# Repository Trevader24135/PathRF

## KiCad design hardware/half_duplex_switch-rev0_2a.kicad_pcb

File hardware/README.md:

# Hardware

The hardware for the PathRF was designed using KiCad 7.0 (available to download for free [here](https://www.kicad.org/download/)).

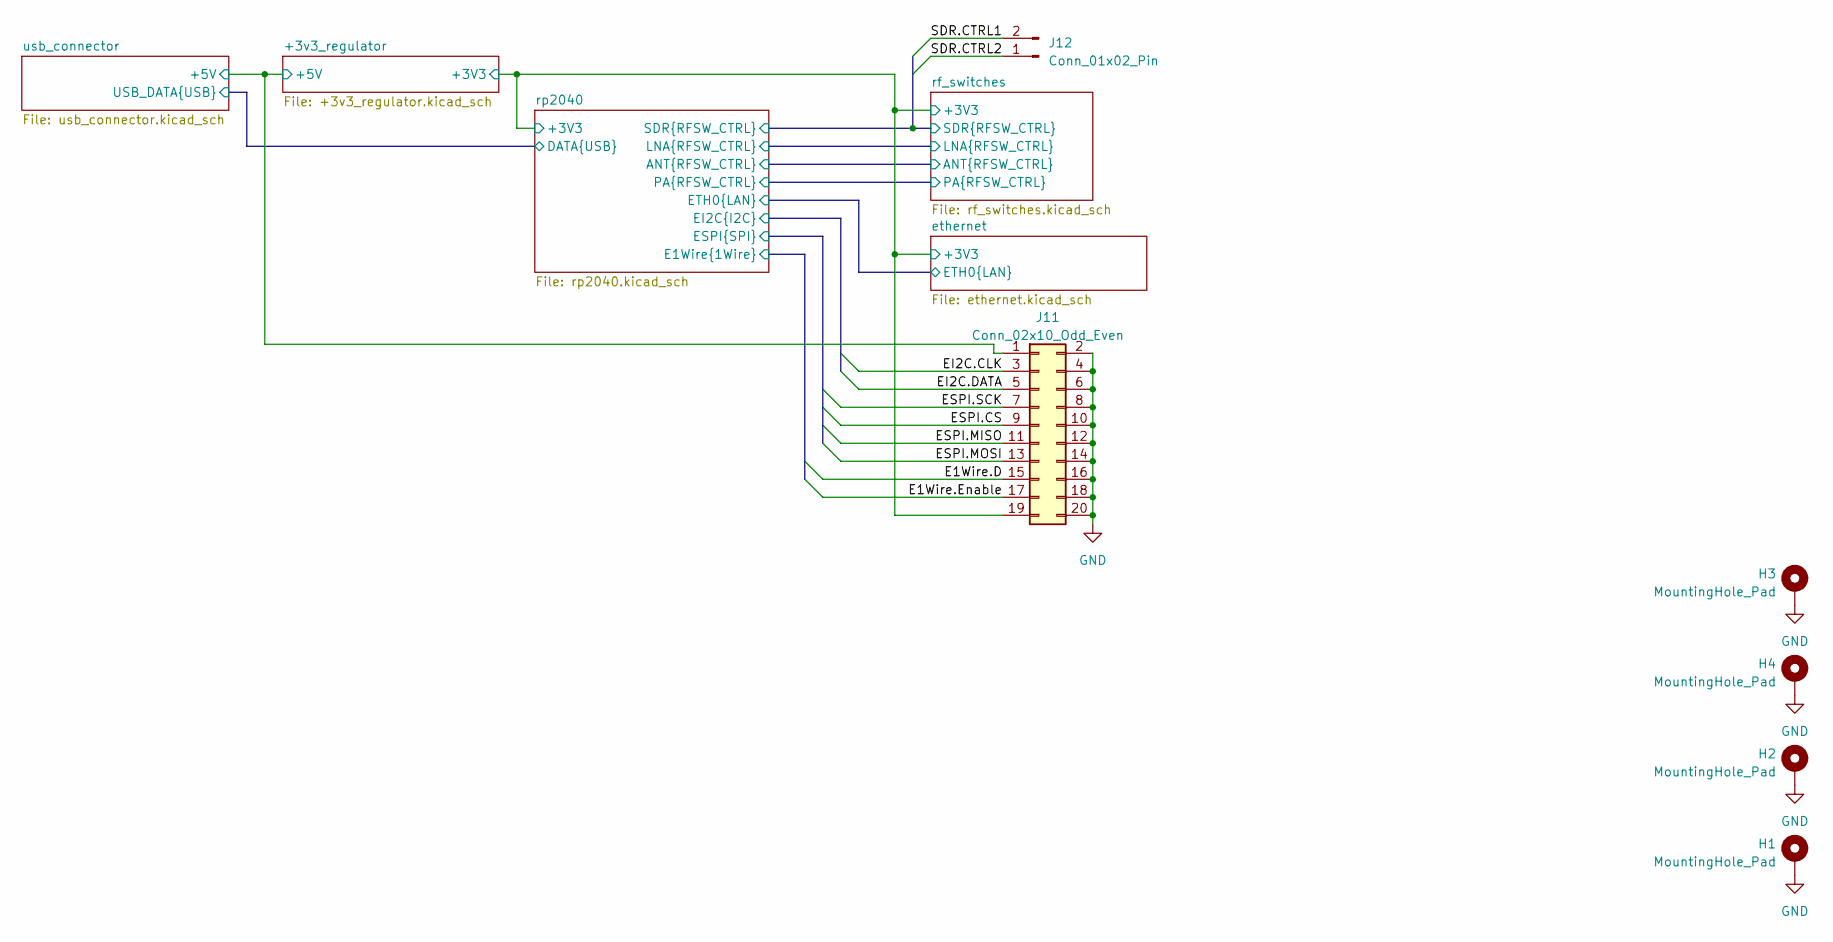
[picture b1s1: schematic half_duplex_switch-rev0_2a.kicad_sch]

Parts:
H1, H2, H3, H4: MountingHole_Pad; MountingHole_3.2mm_M3_Pad_Via
J11: Conn_02x10_Odd_Even; PinSocket_2x10_P2.54mm_Horizontal
J12: Conn_01x02_Pin; PinHeader_1x02_P2.54mm_Vertical

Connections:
/+3v3_regulator/+3V3: J11.19; also elsewhere on the board
/+3v3_regulator/+5V: J11.1; also elsewhere on the board
/rf_switches/SDR.CTRL1: J12.2; also elsewhere on the board
/rf_switches/SDR.CTRL2: J12.1; also elsewhere on the board
/rp2040/E1Wire.D: J11.15; also elsewhere on the board
/rp2040/E1Wire.Enable: J11.17; also elsewhere on the board
/rp2040/EI2C.CLK: J11.3; also elsewhere on the board
/rp2040/EI2C.DATA: J11.5; also elsewhere on the board
/rp2040/ESPI.CS: J11.9; also elsewhere on the board
/rp2040/ESPI.MISO: J11.11; also elsewhere on the board
/rp2040/ESPI.MOSI: J11.13; also elsewhere on the board
/rp2040/ESPI.SCK: J11.7; also elsewhere on the board
GND: H1.1, H2.1, H3.1, H4.1, J11.2, J11.4, J11.6, J11.8, J11.10, J11.12, J11.14, J11.16, J11.18, J11.20; also elsewhere on the board

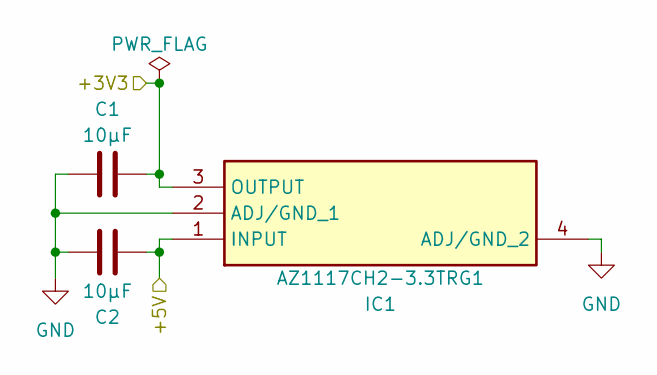
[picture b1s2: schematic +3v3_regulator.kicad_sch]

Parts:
C1, C2: 10μF; C_1206_3216Metric_Pad1.33x1.80mm_HandSolder
IC1: AZ1117CH2-3.3TRG1; SOT230P700X180-4N; Mouser Part Number 621-AZ1117CH2-33TRG1

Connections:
/+3v3_regulator/+3V3: C1.1, IC1.3 (OUTPUT); also elsewhere on the board
/+3v3_regulator/+5V: C2.2, IC1.1 (INPUT); also elsewhere on the board
GND: C1.2, C2.1, IC1.2 (ADJ/GND_1), IC1.4 (ADJ/GND_2); also elsewhere on the board

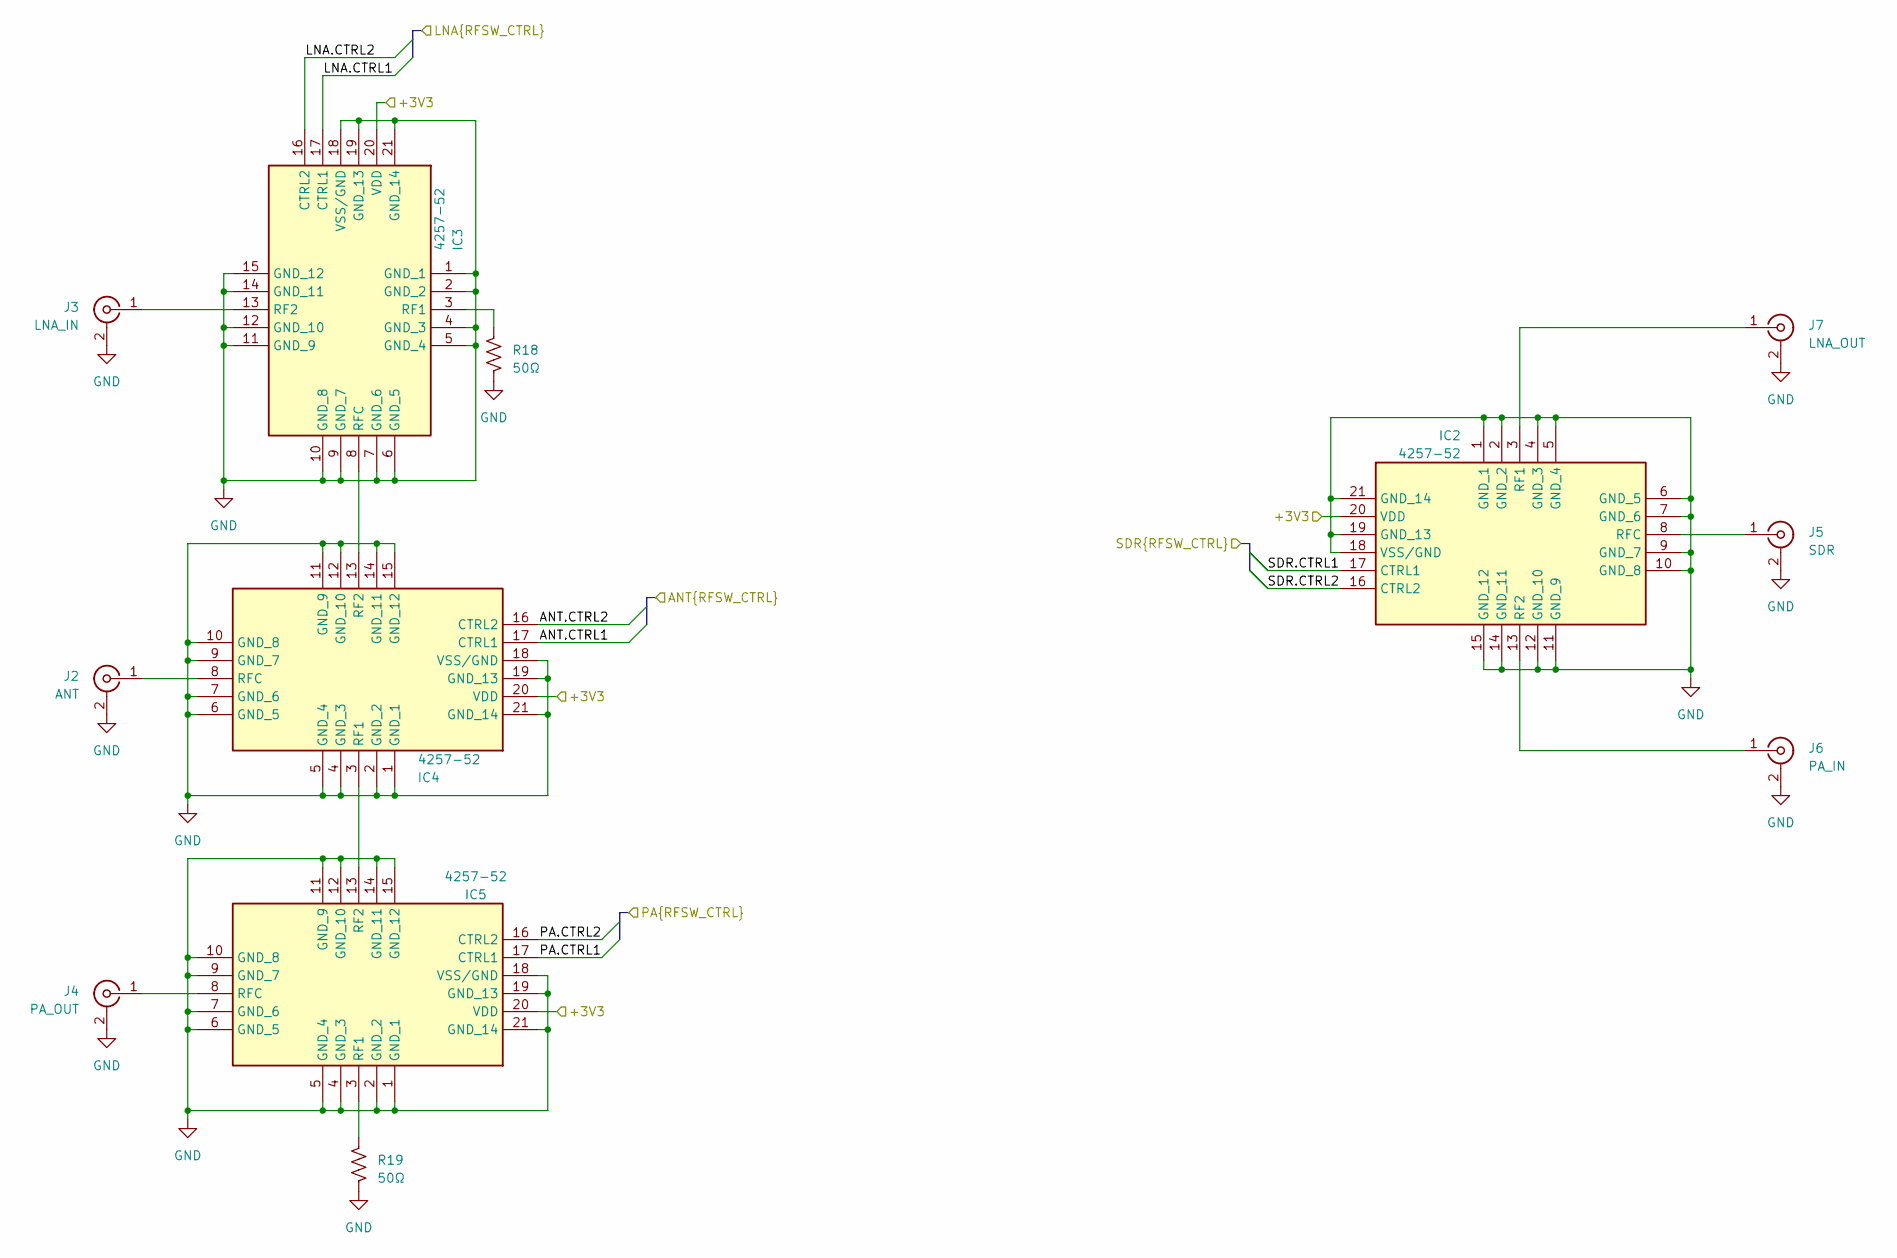
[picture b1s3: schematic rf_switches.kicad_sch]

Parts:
IC2, IC3, IC4, IC5: 4257-52; QFN50P400X400X90-21N; Mouser Part Number 81-4257-52
J2: ANT; SMA_Amphenol_901-143_Horizontal-NoEdge
J3: LNA_IN; SMA_Amphenol_901-143_Horizontal-NoEdge
J4: PA_OUT; SMA_Amphenol_901-143_Horizontal-NoEdge
J5: SDR; SMA_Amphenol_901-143_Horizontal-NoEdge
J6: PA_IN; SMA_Amphenol_901-143_Horizontal-NoEdge
J7: LNA_OUT; SMA_Amphenol_901-143_Horizontal-NoEdge
R18, R19: 50Ω; R_1206_3216Metric_Pad1.30x1.75mm_HandSolder

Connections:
/+3v3_regulator/+3V3: IC2.20 (VDD), IC3.20 (VDD), IC4.20 (VDD), IC5.20 (VDD); also elsewhere on the board
/rf_switches/ANT.CTRL1: IC4.17 (CTRL1); also elsewhere on the board
/rf_switches/ANT.CTRL2: IC4.16 (CTRL2); also elsewhere on the board
/rf_switches/LNA.CTRL1: IC3.17 (CTRL1); also elsewhere on the board
/rf_switches/LNA.CTRL2: IC3.16 (CTRL2); also elsewhere on the board
/rf_switches/PA.CTRL1: IC5.17 (CTRL1); also elsewhere on the board
/rf_switches/PA.CTRL2: IC5.16 (CTRL2); also elsewhere on the board
/rf_switches/SDR.CTRL1: IC2.17 (CTRL1); also elsewhere on the board
/rf_switches/SDR.CTRL2: IC2.16 (CTRL2); also elsewhere on the board
GND: IC2.1 (GND_1), IC2.2 (GND_2), IC2.4 (GND_3), IC2.5 (GND_4), IC2.6 (GND_5), IC2.7 (GND_6), IC2.9 (GND_7), IC2.10 (GND_8), IC2.11 (GND_9), IC2.12 (GND_10), IC2.14 (GND_11), IC2.15 (GND_12), IC2.18 (VSS/GND), IC2.19 (GND_13), IC2.21 (GND_14), IC3.1 (GND_1), IC3.2 (GND_2), IC3.4 (GND_3), IC3.5 (GND_4), IC3.6 (GND_5), IC3.7 (GND_6), IC3.9 (GND_7), IC3.10 (GND_8), IC3.11 (GND_9), IC3.12 (GND_10), IC3.14 (GND_11), IC3.15 (GND_12), IC3.18 (VSS/GND), IC3.19 (GND_13), IC3.21 (GND_14), IC4.1 (GND_1), IC4.2 (GND_2), IC4.4 (GND_3), IC4.5 (GND_4), IC4.6 (GND_5), IC4.7 (GND_6), IC4.9 (GND_7), IC4.10 (GND_8), IC4.11 (GND_9), IC4.12 (GND_10), IC4.14 (GND_11), IC4.15 (GND_12), IC4.18 (VSS/GND), IC4.19 (GND_13), IC4.21 (GND_14), IC5.1 (GND_1), IC5.2 (GND_2), IC5.4 (GND_3), IC5.5 (GND_4), IC5.6 (GND_5), IC5.7 (GND_6), IC5.9 (GND_7), IC5.10 (GND_8), IC5.11 (GND_9), IC5.12 (GND_10), IC5.14 (GND_11), IC5.15 (GND_12), IC5.18 (VSS/GND), IC5.19 (GND_13), IC5.21 (GND_14), J2.2 (Ext), J3.2 (Ext), J4.2 (Ext), J5.2 (Ext), J6.2 (Ext), J7.2 (Ext), R18.2, R19.2; also elsewhere on the board
unnamed: IC2.3 (RF1), J7.1 (In)
unnamed: IC2.13 (RF2), J6.1 (In)
unnamed: IC2.8 (RFC), J5.1 (In)
unnamed: IC3.3 (RF1), R18.1
unnamed: IC3.13 (RF2), J3.1 (In)
unnamed: IC3.8 (RFC), IC4.13 (RF2)
unnamed: IC4.3 (RF1), IC5.13 (RF2)
unnamed: IC4.8 (RFC), J2.1 (In)
unnamed: IC5.3 (RF1), R19.1
unnamed: IC5.8 (RFC), J4.1 (In)

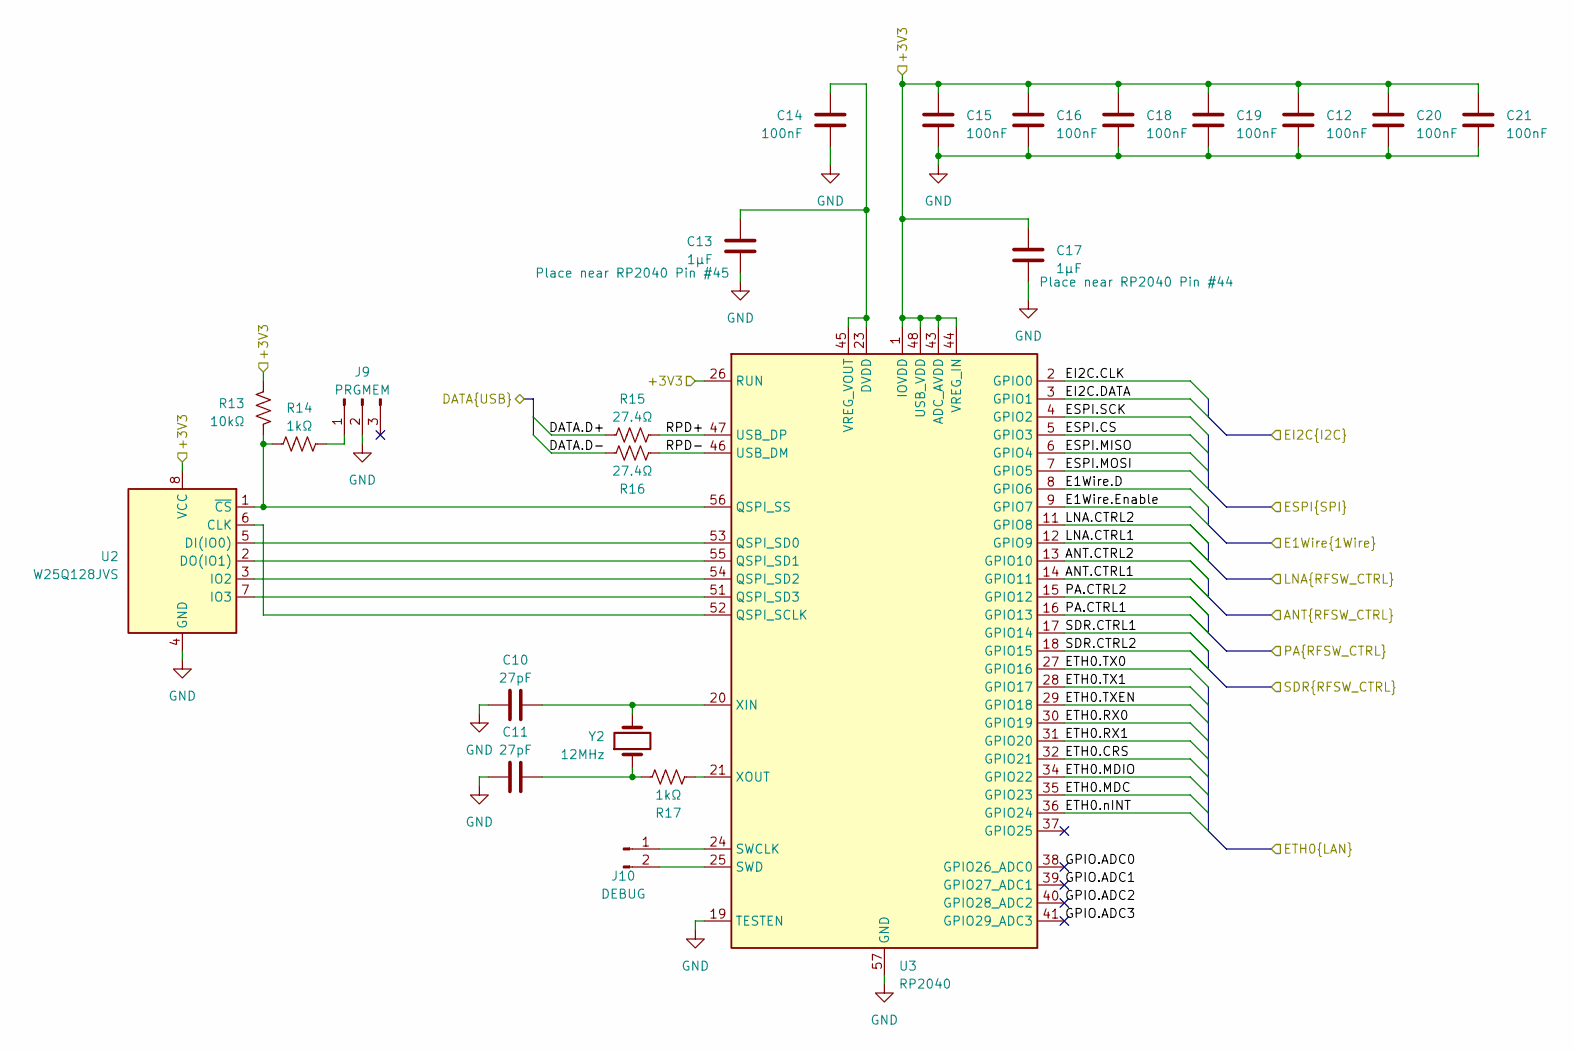
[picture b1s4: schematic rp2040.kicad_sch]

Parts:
C10, C11: 27pF; C_1206_3216Metric_Pad1.33x1.80mm_HandSolder
C12, C14, C15, C16, C18, C19, C20, C21: 100nF; C_1206_3216Metric_Pad1.33x1.80mm_HandSolder
C13, C17: 1μF; C_1206_3216Metric_Pad1.33x1.80mm_HandSolder
J9: PRGMEM; PinHeader_1x03_P2.54mm_Vertical
J10: DEBUG; PinHeader_1x02_P2.54mm_Vertical
R13: 10kΩ; R_1206_3216Metric_Pad1.30x1.75mm_HandSolder
R14, R17: 1kΩ; R_1206_3216Metric_Pad1.30x1.75mm_HandSolder
R15, R16: 27.4Ω; R_1206_3216Metric_Pad1.30x1.75mm_HandSolder
U2: W25Q128JVS; SOIC-8_5.23x5.23mm_P1.27mm
U3: RP2040; QFN-56-1EP_7x7mm_P0.4mm_EP3.2x3.2mm
Y2: 12MHz; Crystal_HC49-4H_Vertical

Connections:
/+3v3_regulator/+3V3: C12.1, C15.1, C16.1, C17.1, C18.1, C19.1, C20.1, C21.1, R13.2, U2.8 (VCC), U3.1 (IOVDD), U3.10 (IOVDD), U3.22 (IOVDD), U3.26 (RUN), U3.33 (IOVDD), U3.42 (IOVDD), U3.43 (ADC_AVDD), U3.44 (VREG_IN), U3.48 (USB_VDD), U3.49 (IOVDD); also elsewhere on the board
/ethernet/ETH0.CRS: U3.32 (GPIO21); also elsewhere on the board
/ethernet/ETH0.MDC: U3.35 (GPIO23); also elsewhere on the board
/ethernet/ETH0.MDIO: U3.34 (GPIO22); also elsewhere on the board
/ethernet/ETH0.RX0: U3.30 (GPIO19); also elsewhere on the board
/ethernet/ETH0.RX1: U3.31 (GPIO20); also elsewhere on the board
/ethernet/ETH0.TX0: U3.27 (GPIO16); also elsewhere on the board
/ethernet/ETH0.TX1: U3.28 (GPIO17); also elsewhere on the board
/ethernet/ETH0.TXEN: U3.29 (GPIO18); also elsewhere on the board
/ethernet/ETH0.nINT: U3.36 (GPIO24); also elsewhere on the board
/rf_switches/ANT.CTRL1: U3.14 (GPIO11); also elsewhere on the board
/rf_switches/ANT.CTRL2: U3.13 (GPIO10); also elsewhere on the board
/rf_switches/LNA.CTRL1: U3.12 (GPIO9); also elsewhere on the board
/rf_switches/LNA.CTRL2: U3.11 (GPIO8); also elsewhere on the board
/rf_switches/PA.CTRL1: U3.16 (GPIO13); also elsewhere on the board
/rf_switches/PA.CTRL2: U3.15 (GPIO12); also elsewhere on the board
/rf_switches/SDR.CTRL1: U3.17 (GPIO14); also elsewhere on the board
/rf_switches/SDR.CTRL2: U3.18 (GPIO15); also elsewhere on the board
/rp2040/DATA.D+: R15.1; also elsewhere on the board
/rp2040/DATA.D-: R16.1; also elsewhere on the board
/rp2040/E1Wire.D: U3.8 (GPIO6); also elsewhere on the board
/rp2040/E1Wire.Enable: U3.9 (GPIO7); also elsewhere on the board
/rp2040/EI2C.CLK: U3.2 (GPIO0); also elsewhere on the board
/rp2040/EI2C.DATA: U3.3 (GPIO1); also elsewhere on the board
/rp2040/ESPI.CS: U3.5 (GPIO3); also elsewhere on the board
/rp2040/ESPI.MISO: U3.6 (GPIO4); also elsewhere on the board
/rp2040/ESPI.MOSI: U3.7 (GPIO5); also elsewhere on the board
/rp2040/ESPI.SCK: U3.4 (GPIO2); also elsewhere on the board
/rp2040/GPIO.ADC0: U3.38 (GPIO26_ADC0)
/rp2040/GPIO.ADC1: U3.39 (GPIO27_ADC1)
/rp2040/GPIO.ADC2: U3.40 (GPIO28_ADC2)
/rp2040/GPIO.ADC3: U3.41 (GPIO29_ADC3)
/rp2040/RPD+: R15.2, U3.47 (USB_DP)
/rp2040/RPD-: R16.2, U3.46 (USB_DM)
GND: C10.1, C11.1, C12.2, C13.2, C14.2, C15.2, C16.2, C17.2, C18.2, C19.2, C20.2, C21.2, J9.2, U2.4 (GND), U3.19 (TESTEN), U3.57 (GND); also elsewhere on the board
unnamed: C11.2, R17.2, Y2.1
unnamed: J9.1, R14.2
unnamed: J10.1, U3.24 (SWCLK)
unnamed: J10.2, U3.25 (SWD)
unnamed: U2.6 (CLK), U3.52 (QSPI_SCLK)
unnamed: U2.5 (DI(IO0)), U3.53 (QSPI_SD0)
unnamed: U2.2 (DO(IO1)), U3.55 (QSPI_SD1)
unnamed: U2.3 (IO2), U3.54 (QSPI_SD2)
unnamed: U2.7 (IO3), U3.51 (QSPI_SD3)
unnamed: R13.1, R14.1, U2.1 (~CS), U3.56 (QSPI_SS)
unnamed: C13.1, C14.1, U3.23 (DVDD), U3.45 (VREG_VOUT), U3.50 (DVDD)
unnamed: C10.2, U3.20 (XIN), Y2.2
unnamed: R17.1, U3.21 (XOUT)

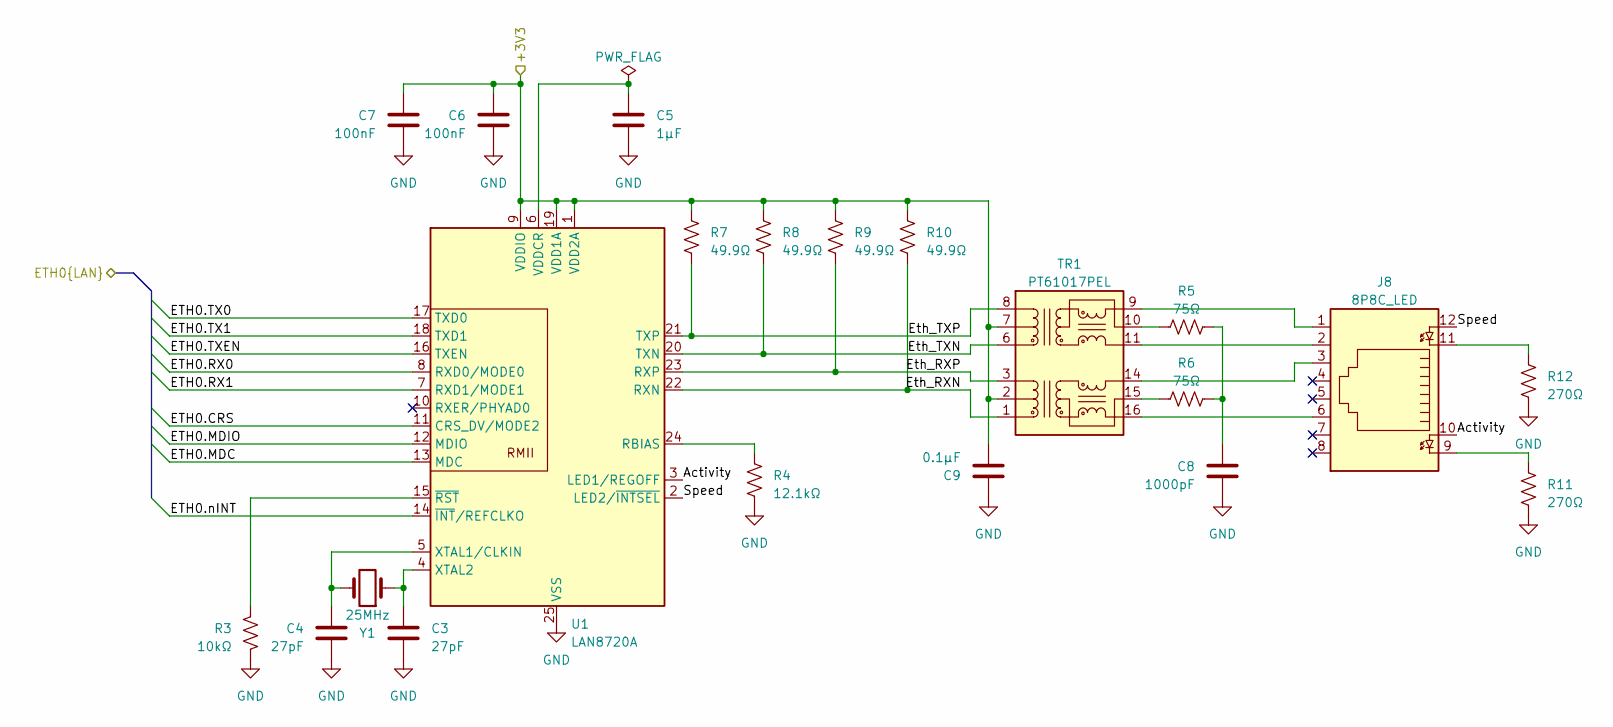
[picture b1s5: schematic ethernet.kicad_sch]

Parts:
C3, C4: 27pF; C_1206_3216Metric_Pad1.33x1.80mm_HandSolder
C5: 1μF; C_1206_3216Metric_Pad1.33x1.80mm_HandSolder
C6, C7: 100nF; C_1206_3216Metric_Pad1.33x1.80mm_HandSolder
C8: 1000pF; C_1812_4532Metric_Pad1.57x3.40mm_HandSolder
C9: 0.1μF; C_1206_3216Metric_Pad1.33x1.80mm_HandSolder
J8: 8P8C_LED; RJHSE5086
R3: 10kΩ; R_1206_3216Metric_Pad1.30x1.75mm_HandSolder
R4: 12.1kΩ; R_1206_3216Metric_Pad1.30x1.75mm_HandSolder
R5, R6: 75Ω; R_1206_3216Metric_Pad1.30x1.75mm_HandSolder
R7, R8, R9, R10: 49.9Ω; R_1206_3216Metric_Pad1.30x1.75mm_HandSolder
R11, R12: 270Ω; R_1206_3216Metric_Pad1.30x1.75mm_HandSolder
TR1: PT61017PEL; Transformer_Ethernet_Bourns_PT61017PEL
U1: LAN8720A; VQFN-24-1EP_4x4mm_P0.5mm_EP2.5x2.5mm_ThermalVias
Y1: 25MHz; Crystal_HC49-4H_Vertical

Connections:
/+3v3_regulator/+3V3: C6.1, C7.1, C9.2, R7.1, R8.1, R9.1, R10.1, TR1.2 (C_TD), TR1.7 (C_RD), U1.1 (VDD2A), U1.9 (VDDIO), U1.19 (VDD1A); also elsewhere on the board
/ethernet/Activity: J8.10, U1.3 (LED1/REGOFF)
/ethernet/ETH0.CRS: U1.11 (CRS_DV/MODE2); also elsewhere on the board
/ethernet/ETH0.MDC: U1.13 (MDC); also elsewhere on the board
/ethernet/ETH0.MDIO: U1.12 (MDIO); also elsewhere on the board
/ethernet/ETH0.RX0: U1.8 (RXD0/MODE0); also elsewhere on the board
/ethernet/ETH0.RX1: U1.7 (RXD1/MODE1); also elsewhere on the board
/ethernet/ETH0.TX0: U1.17 (TXD0); also elsewhere on the board
/ethernet/ETH0.TX1: U1.18 (TXD1); also elsewhere on the board
/ethernet/ETH0.TXEN: U1.16 (TXEN); also elsewhere on the board
/ethernet/ETH0.nINT: U1.14 (~INT/REFCLKO); also elsewhere on the board
/ethernet/Eth_RXN: R10.2, TR1.1 (TD+), U1.22 (RXN)
/ethernet/Eth_RXP: R9.2, TR1.3 (TD-), U1.23 (RXP)
/ethernet/Eth_TXN: R8.2, TR1.6 (RD+), U1.20 (TXN)
/ethernet/Eth_TXP: R7.2, TR1.8 (RD-), U1.21 (TXP)
/ethernet/Speed: J8.12, U1.2 (LED2/~INTSEL)
GND: C3.2, C4.2, C5.2, C6.2, C7.2, C8.2, C9.1, R3.1, R4.2, R11.1, R12.1, U1.25 (VSS); also elsewhere on the board
unnamed: C8.1, R5.2, R6.2
unnamed: J8.9, R11.2
unnamed: J8.11, R12.2
unnamed: R5.1, TR1.10 (C_RX)
unnamed: R6.1, TR1.15 (C_TX)
unnamed: J8.2, TR1.11 (RX+)
unnamed: J8.1, TR1.9 (RX-)
unnamed: J8.6, TR1.16 (TX+)
unnamed: J8.3, TR1.14 (TX-)
unnamed: R4.1, U1.24 (RBIAS)
unnamed: C5.1, U1.6 (VDDCR)
unnamed: C4.1, U1.5 (XTAL1/CLKIN), Y1.2
unnamed: C3.1, U1.4 (XTAL2), Y1.1
unnamed: R3.2, U1.15 (~RST)

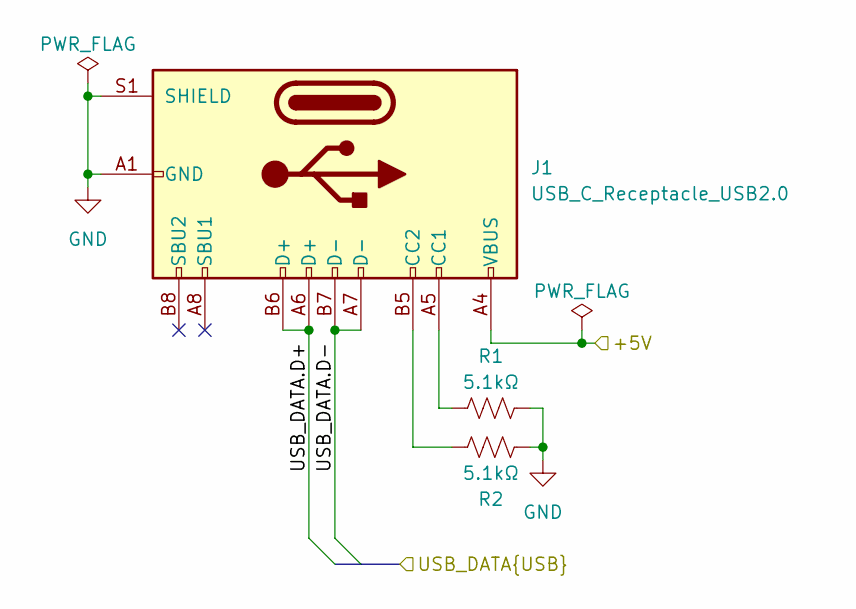
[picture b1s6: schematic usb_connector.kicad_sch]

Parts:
J1: USB_C_Receptacle_USB2.0; USB_C_Receptacle_GCT_USB4085
R1, R2: 5.1kΩ; R_1206_3216Metric_Pad1.30x1.75mm_HandSolder

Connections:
/+3v3_regulator/+5V: J1.A4 (VBUS), J1.A9 (VBUS), J1.B4 (VBUS), J1.B9 (VBUS); also elsewhere on the board
/rp2040/DATA.D+: J1.A6 (D+), J1.B6 (D+); also elsewhere on the board
/rp2040/DATA.D-: J1.A7 (D-), J1.B7 (D-); also elsewhere on the board
GND: J1.A1 (GND), J1.A12 (GND), J1.B1 (GND), J1.B12 (GND), J1.S1 (SHIELD), R1.2, R2.1; also elsewhere on the board
unnamed: J1.A5 (CC1), R1.1
unnamed: J1.B5 (CC2), R2.2

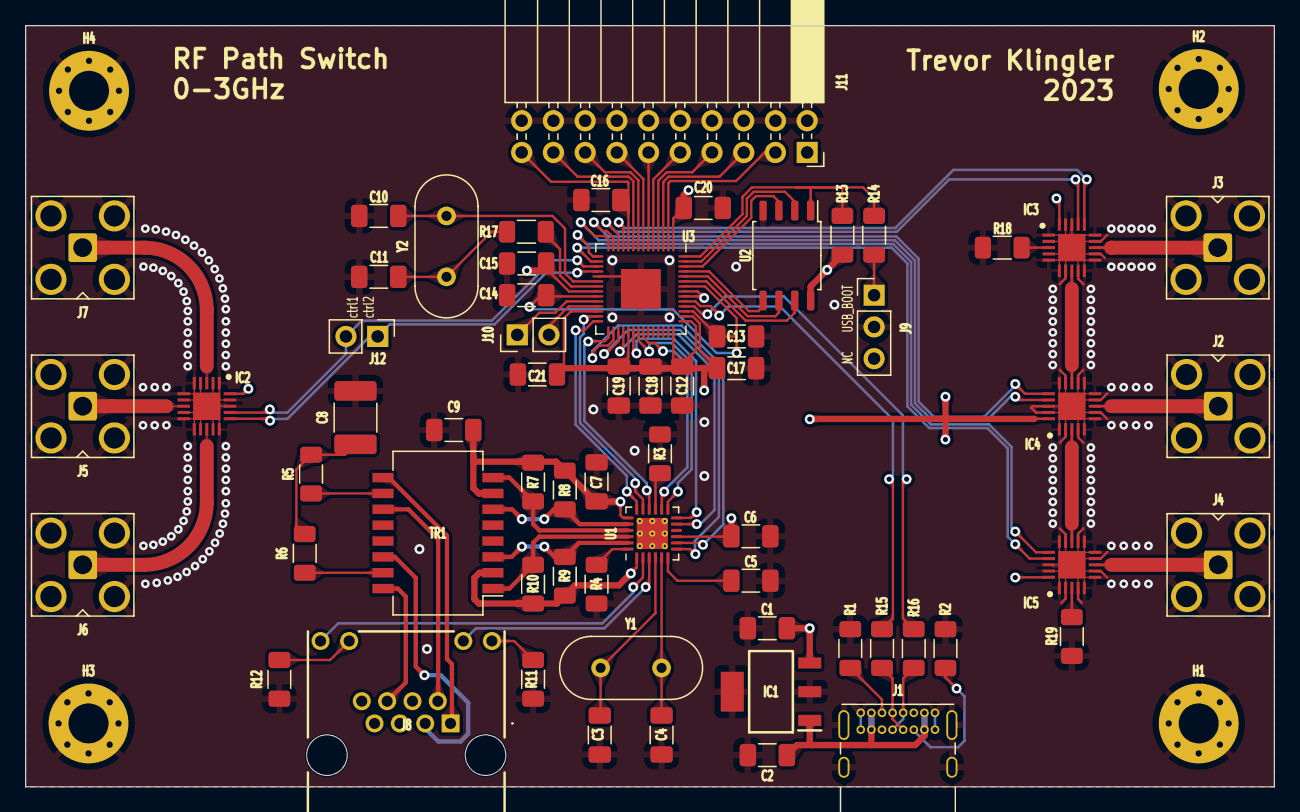
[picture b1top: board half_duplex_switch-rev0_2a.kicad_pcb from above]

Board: 4 copper layers, 100.0 x 61.0 mm, 67 parts (0 on the bottom side), 77 nets.

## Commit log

2023-07-11 feat: Add KiCad hardware project. Structure Repo.
    Added the KiCad project into the hardware folder. The structure for the
    firmware was created, but currently only contains readmes.
